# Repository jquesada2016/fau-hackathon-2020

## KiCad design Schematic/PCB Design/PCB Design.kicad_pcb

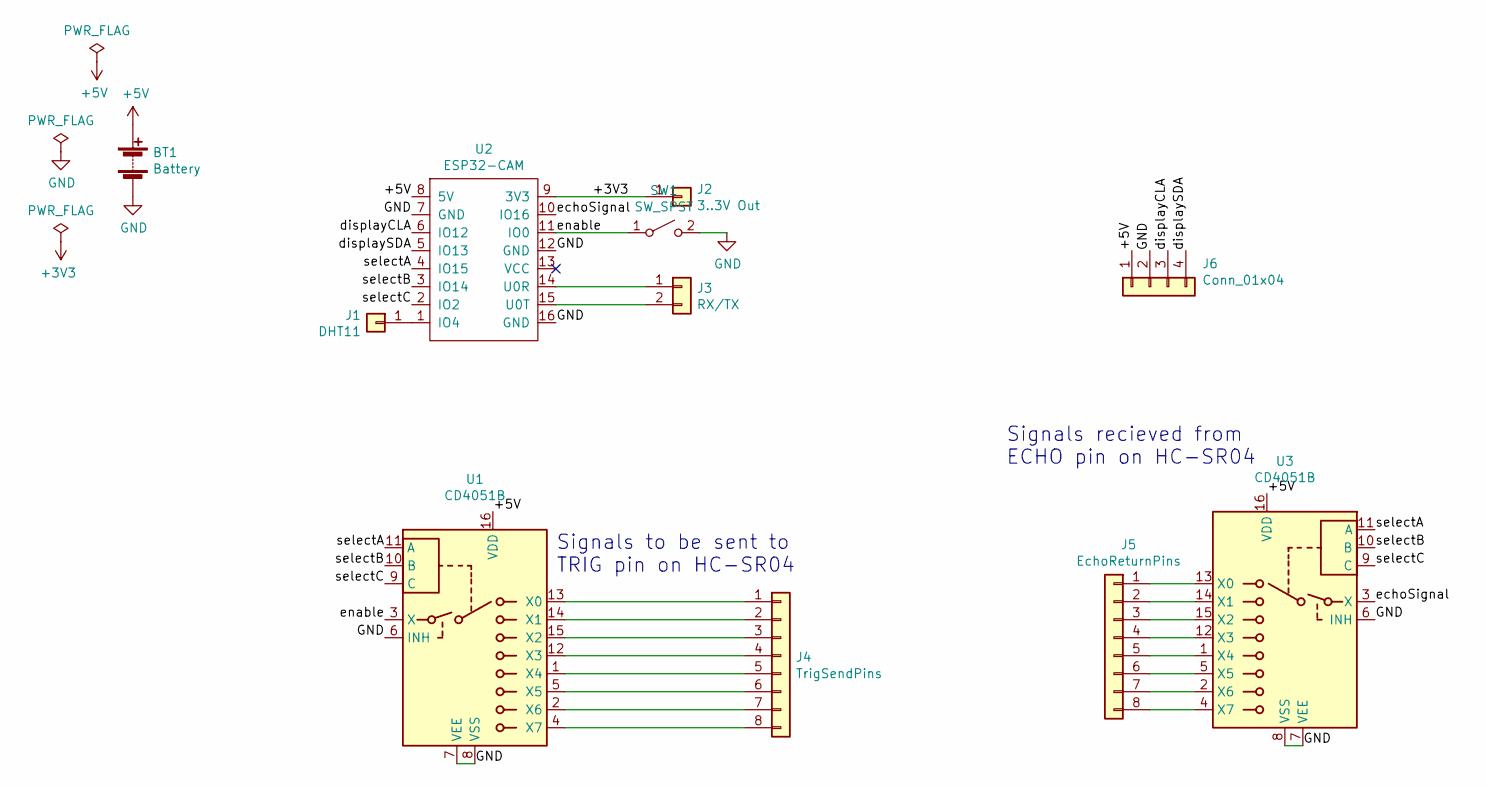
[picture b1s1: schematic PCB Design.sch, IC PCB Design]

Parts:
BT1: Battery; conn_01x02_battery
J1: DHT11; conn_01x01
J2: 3..3V Out; conn_01x01
J3: RX/TX; conn_01x02
J4: TrigSendPins; conn_01x08
J5: EchoReturnPins; conn_01x08
J6: Conn_01x04; conn_01x04
SW1: SW_SPST
U1, U3: CD4051B; DIP-16_W7.62mm
U2: ESP32-CAM; ESP32CAM

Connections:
+3V3: J2.1, U2.9 (3V3)
+5V: BT1.1 (+), J6.1, U1.16 (VDD), U2.8 (5V), U3.16 (VDD)
/displayCLA: J6.3, U2.6 (IO12)
/displaySDA: J6.4, U2.5 (IO13)
/echoSignal: U2.10 (IO16), U3.3 (X)
/enable: SW1.1 (A), U1.3 (X), U2.11 (IO0)
/selectA: U1.11 (A), U2.4 (IO15), U3.11 (A)
/selectB: U1.10 (B), U2.3 (IO14), U3.10 (B)
/selectC: U1.9 (C), U2.2 (IO2), U3.9 (C)
GND: BT1.2 (-), J6.2, SW1.2 (B), U1.6 (INH), U1.7 (VEE), U1.8 (VSS), U2.7 (GND), U2.12 (GND), U2.16 (GND), U3.6 (INH), U3.7 (VEE), U3.8 (VSS)
unnamed: J1.1, U2.1 (IO4)
unnamed: J3.1, U2.14 (U0R)
unnamed: J3.2, U2.15 (U0T)
unnamed: J4.1, U1.13 (X0)
unnamed: J4.2, U1.14 (X1)
unnamed: J4.3, U1.15 (X2)
unnamed: J4.4, U1.12 (X3)
unnamed: J4.5, U1.1 (X4)
unnamed: J4.6, U1.5 (X5)
unnamed: J4.7, U1.2 (X6)
unnamed: J4.8, U1.4 (X7)
unnamed: J5.1, U3.13 (X0)
unnamed: J5.2, U3.14 (X1)
unnamed: J5.3, U3.15 (X2)
unnamed: J5.4, U3.12 (X3)
unnamed: J5.5, U3.1 (X4)
unnamed: J5.6, U3.5 (X5)
unnamed: J5.7, U3.2 (X6)
unnamed: J5.8, U3.4 (X7)

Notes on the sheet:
Signals recieved from ECHO pin on HC-SR04
Signals to be sent to TRIG pin on HC-SR04

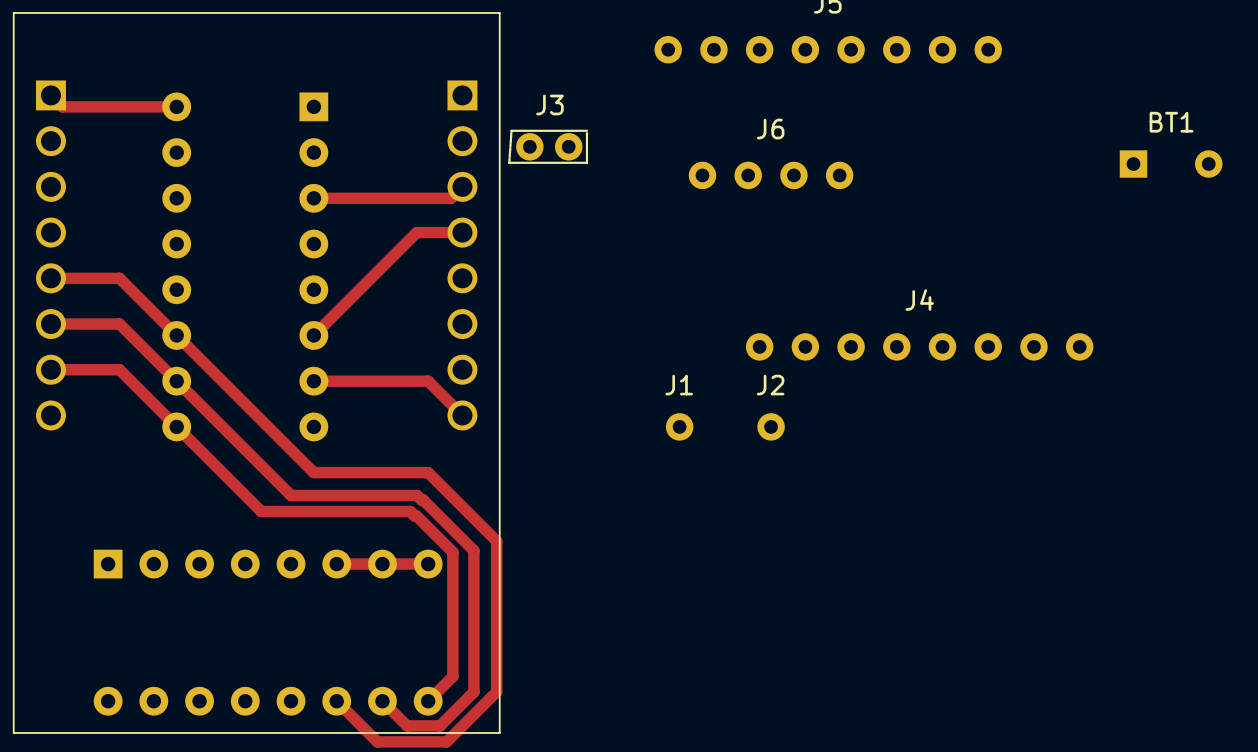
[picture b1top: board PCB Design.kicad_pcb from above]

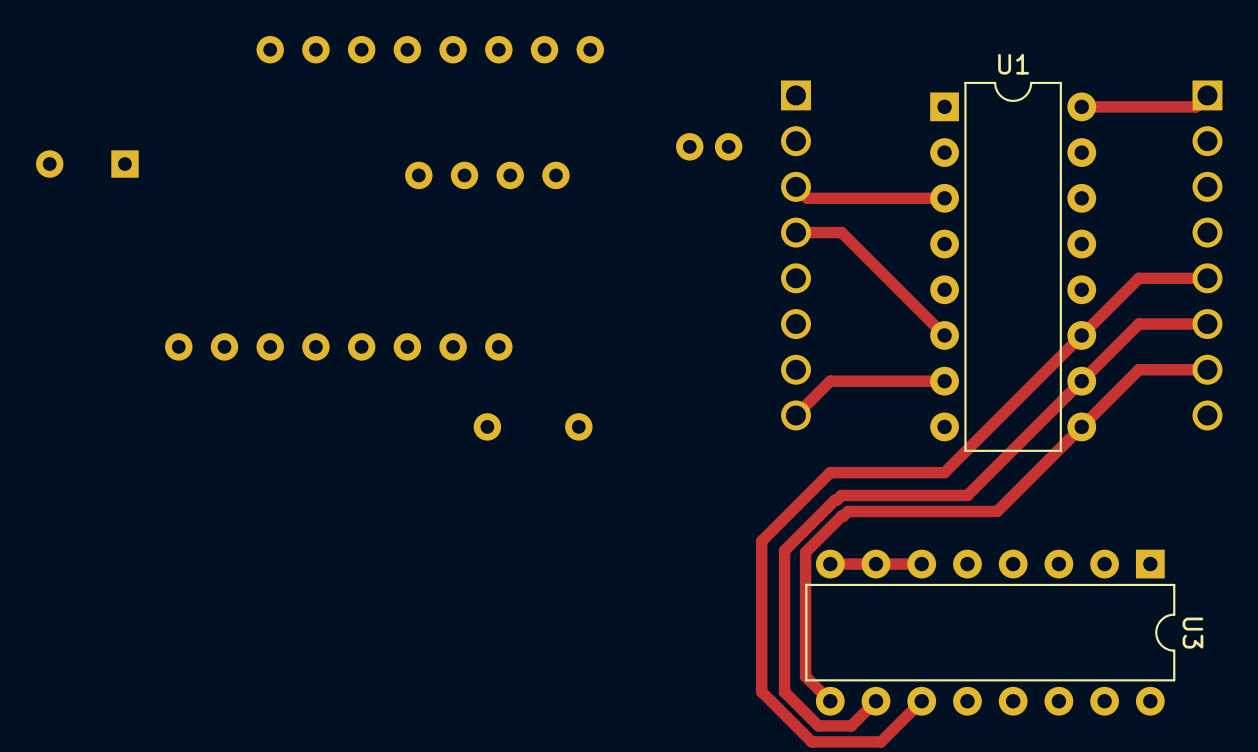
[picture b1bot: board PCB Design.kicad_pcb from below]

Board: 2 copper layers, 10 parts (2 on the bottom side), 29 nets.

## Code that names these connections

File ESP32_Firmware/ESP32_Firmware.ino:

#include "esp_camera.h"
#include <Wire.h>
#include <WiFi.h>
#include "SPIFFS.h"
#include "ESPAsyncWebServer.h"
#include "SSD1306.h"
#include <qrcode.h>

#define DHTTYPE DHT11


// Define pins
#define SELECTA0 15
#define SELECTA1 14
#define SELECTA2 2
#define ENABLE 4
#define ECHOSIGNAL 16
#define DISPLAYCLA 12
#define DISPLAYSDA 13
#define DHT11 0


// Function declerations
void select0();
void select1();
void select2();
void select3();
void select4();
void select5();
void select6();
void select7();

void findClosestObject(float values[]);
double getDistance(int sensorNumber);
void triggerSensor();
float getTemp();


SSD1306 display(0x3c, DISPLAYSDA, DISPLAYCLA);
QRcode qrcode(&display);
AsyncWebServer server(80);


const char* ssid = "Jose's Galaxy Note10+";
const char* password = "4077759622";


const char* file1 = "/index.html";
const char* file2 = "/app.js";
const char* file3 = "/styles.css";
const char* JAVASCRIPT = "text/javascript";
const char* CSS = "text/css";
const char* JSON = "text/json";


void setup() {
  Serial.begin(115200);
  Serial.setDebugOutput(true);
  Serial.println();

  // Pin mode setup
  pinMode(SELECTA0, OUTPUT);
  pinMode(SELECTA1, OUTPUT);
  pinMode(SELECTA2, OUTPUT);
  pinMode(DISPLAYSDA, OUTPUT);
  pinMode(DISPLAYCLA, OUTPUT);
  pinMode(ENABLE, OUTPUT);
  pinMode(ECHOSIGNAL, INPUT);
  pinMode(DHT11, INPUT);


  if (!SPIFFS.begin()) {
    Serial.println("it broke #SPIFFS");
  }
  WiFi.begin(ssid, password);

  while (WiFi.status() != WL_CONNECTED) {
    delay(500);
    Serial.print(".");
  }
  Serial.println("");
  Serial.println("WiFi connected");

  Serial.print("WiFi Ready! Use 'http://");
  Serial.print(WiFi.localIP());
  Serial.println("' to connect");

  // Create IP address link.
  const char* http = "http://";
  const String local_ip = WiFi.localIP().toString();
  const String address = http + local_ip;

  // Create web server routes
  server.on("/", HTTP_GET, [](AsyncWebServerRequest *request){
    Serial.println("Serving /");
    request->send(SPIFFS, "/index.html", "text/html");
  });
  server.on(file2, HTTP_GET, [](AsyncWebServerRequest *request) {
    Serial.println("Serving JS 1");
    request->send(SPIFFS, file2, JAVASCRIPT);
  });
  server.on(file3, HTTP_GET, [](AsyncWebServerRequest *request) {
    Serial.println("Serving JS 2");
    request->send(SPIFFS, file3, CSS);
  });
  server.on("/closestProximity", HTTP_GET, [](AsyncWebServerRequest *request) {
    Serial.println("Serving API call to /closestProximity");
    float values[2];
    findClosestObject(values);
    Serial.println("Finished findClossestObject()");

    String json = "{\"sensor\": " + String(values[0]) + ", \"distance\": " + String(values[1]) + "}";
    
    request->send(200, JSON, json);
  });
  
  
  server.begin();
  
  //display.init();
  //qrcode.init();

  // Display the address as a QR code.
  //qrcode.create(address);
}

void loop() {}


// Function definitions
void select0() {
  digitalWrite(SELECTA0, LOW);
  digitalWrite(SELECTA1, LOW);
  digitalWrite(SELECTA2, LOW);
}

void select1() {
  digitalWrite(SELECTA0, HIGH);
  digitalWrite(SELECTA1, LOW);
  digitalWrite(SELECTA2, LOW);
}

void select2() {
  digitalWrite(SELECTA0, LOW);
  digitalWrite(SELECTA1, HIGH);
  digitalWrite(SELECTA2, LOW);
}

void select3() {
  digitalWrite(SELECTA0, HIGH);
  digitalWrite(SELECTA1, HIGH);
  digitalWrite(SELECTA2, LOW);
}

void select4() {
  digitalWrite(SELECTA0, LOW);
  digitalWrite(SELECTA1, LOW);
  digitalWrite(SELECTA2, HIGH);
}

void select5() {
  digitalWrite(SELECTA0, HIGH);
  digitalWrite(SELECTA1, LOW);
  digitalWrite(SELECTA2, HIGH);
}

void select6() {
  digitalWrite(SELECTA0, LOW);
  digitalWrite(SELECTA1, HIGH);
  digitalWrite(SELECTA2, HIGH);
}

void select7() {
  digitalWrite(SELECTA0, HIGH);
  digitalWrite(SELECTA1, HIGH);
  digitalWrite(SELECTA2, HIGH);
}

void triggerSensor() {
  digitalWrite(ENABLE, LOW);
  delayMicroseconds(5);
  digitalWrite(ENABLE, HIGH);
  delayMicroseconds(10);
  digitalWrite(ENABLE, LOW);
}

float getTemp() {
  return 20 + 273.15;  
}

double getDistance(int sensorNumber) {
    switch (sensorNumber) {
      long duration;
      
      case 0:
        select0();
        triggerSensor();
        duration = pulseIn(ECHOSIGNAL, HIGH);
        return (duration/2.0) * (0.00002005 * sqrt(getTemp()));
      case 1:
        select1();
        triggerSensor();
        duration = pulseIn(ECHOSIGNAL, HIGH);
        return (duration/2.0) * (0.00002005 * sqrt(getTemp()));
      case 2:
        select2();
        triggerSensor();
        duration = pulseIn(ECHOSIGNAL, HIGH);
        return (duration/2.0) * (0.00002005 * sqrt(getTemp()));
      case 3:
        select3();
        triggerSensor();
        duration = pulseIn(ECHOSIGNAL, HIGH);
        return (duration/2.0) * (0.00002005 * sqrt(getTemp()));
      case 4:
        select4();
        triggerSensor();
        duration = pulseIn(ECHOSIGNAL, HIGH);
        return (duration/2.0) * (0.00002005 * sqrt(getTemp()));
      case 5:
        select5();
        triggerSensor();
        duration = pulseIn(ECHOSIGNAL, HIGH);
        return (duration/2.0) * (0.00002005 * sqrt(getTemp()));
      case 6:
        select6();
        triggerSensor();
        duration = pulseIn(ECHOSIGNAL, HIGH);
        return (duration/2.0) * (0.00002005 * sqrt(getTemp()));
      case 7:
        select7();
        triggerSensor();
        duration = pulseIn(ECHOSIGNAL, HIGH);
        return (duration/2.0) * (0.00002005 * sqrt(getTemp()));
      default:
        Serial.println("Error, you suck. The switch statement failed.");
        
    }
}

void findClosestObject(float values[]) {
  float distance = 9999999;
  for (int i = 0; i < 8; i++) {
    float current_distance = getDistance(i);
    if (current_distance < distance) {
      distance = current_distance;
      values[0] = i;
      values[1] = distance;
    }
  }
}

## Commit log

2020-02-10 set up git repo with initial implementation of QR Reader
2020-02-10 added redamentary QR scanning to ESP32
2020-02-13 created rough architectual schematic"
2020-02-14 added a 8 to 1 mux to select the sensor to listen to
2020-02-19 finished PCB
2020-02-28 Post Hackathon commit
2020-02-29 initiated rev 2A of the board design
2025-06-24 Bump pbkdf2 from 3.0.17 to 3.1.3 in /qrscanner
    ---
    updated-dependencies:
    - dependency-name: pbkdf2
    dependency-version: 3.1.3
    dependency-type: indirect
    ...
2025-07-17 Bump on-headers and compression in /qrscanner
    Bumps [on-headers](https://github.com/jshttp/on-headers) and [compression](https://github.com/expressjs/compression). These dependencies needed to be updated together.
    Updates `on-headers` from 1.0.2 to 1.1.0
    - [Release notes](https://github.com/jshttp/on-headers/releases)
    - [Changelog](https://github.com/jshttp/on-headers/blob/master/HISTORY.md)
    - [Commits](https://github.com/jshttp/on-headers/compare/v1.0.2...v1.1.0)
    Updates `compression` from 1.7.4 to 1.8.1
2025-08-21 Bump sha.js from 2.4.11 to 2.4.12 in /qrscanner
    Bumps [sha.js](https://github.com/crypto-browserify/sha.js) from 2.4.11 to 2.4.12.
    - [Changelog](https://github.com/browserify/sha.js/blob/master/CHANGELOG.md)
    - [Commits](https://github.com/crypto-browserify/sha.js/compare/v2.4.11...v2.4.12)
    ---
    updated-dependencies:
    - dependency-name: sha.js
2025-08-21 Bump cipher-base from 1.0.4 to 1.0.6 in /qrscanner
    Bumps [cipher-base](https://github.com/crypto-browserify/cipher-base) from 1.0.4 to 1.0.6.
    - [Changelog](https://github.com/browserify/cipher-base/blob/master/CHANGELOG.md)
    - [Commits](https://github.com/crypto-browserify/cipher-base/compare/v1.0.4...v1.0.6)
    ---
    updated-dependencies:
    - dependency-name: cipher-base
2025-09-10 Bump shell-quote and react-scripts in /qrscanner
    Bumps [shell-quote](https://github.com/ljharb/shell-quote) to 1.8.3 and updates ancestor dependency [react-scripts](https://github.com/facebook/create-react-app/tree/HEAD/packages/react-scripts). The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
    Updates `shell-quote` from 1.7.2 to 1.8.3
    - [Changelog](https://github.com/ljharb/shell-quote/blob/main/CHANGELOG.md)
    - [Commits](https://github.com/ljharb/shell-quote/compare/v1.7.2...v1.8.3)
    Updates `react-scripts` from 3.3.1 to 5.0.1
    - [Release notes](https://github.com/facebook/create-react-app/releases)
2025-11-18 Bump js-yaml from 3.13.1 to 3.14.2 in /qrscanner
    Bumps [js-yaml](https://github.com/nodeca/js-yaml) from 3.13.1 to 3.14.2.
    - [Changelog](https://github.com/nodeca/js-yaml/blob/master/CHANGELOG.md)
    - [Commits](https://github.com/nodeca/js-yaml/compare/3.13.1...3.14.2)
    ---
    updated-dependencies:
    - dependency-name: js-yaml
2025-11-27 Bump node-forge and react-scripts in /qrscanner
    Bumps [node-forge](https://github.com/digitalbazaar/forge) to 1.3.2 and updates ancestor dependency [react-scripts](https://github.com/facebook/create-react-app/tree/HEAD/packages/react-scripts). The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
    Updates `node-forge` from 0.9.0 to 1.3.2
    - [Changelog](https://github.com/digitalbazaar/forge/blob/main/CHANGELOG.md)
    - [Commits](https://github.com/digitalbazaar/forge/compare/0.9.0...v1.3.2)
    Updates `react-scripts` from 3.3.1 to 5.0.1
    - [Release notes](https://github.com/facebook/create-react-app/releases)
2025-12-31 Bump qs and react-scripts in /qrscanner
    Bumps [qs](https://github.com/ljharb/qs) to 6.14.1 and updates ancestor dependency [react-scripts](https://github.com/facebook/create-react-app/tree/HEAD/packages/react-scripts). These dependencies n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
    Updates `qs` from 6.7.0 to 6.14.1
    - [Changelog](https://github.com/ljharb/qs/blob/main/CHANGELOG.md)
    - [Commits](https://github.com/ljharb/qs/compare/v6.7.0...v6.14.1)
    Updates `react-scripts` from 3.3.1 to 5.0.1
    - [Release notes](https://github.com/facebook/create-react-app/releases)
2026-01-17 Bump tar and fsevents in /qrscanner
    Removes [tar](https://github.com/isaacs/node-tar). It's no longer used after updating ancestor dependency [fsevents](https://github.com/fsevents/fsevents). These dependencies need to be updated toget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
    Removes `tar`
    Updates `fsevents` from 1.2.11 to 1.2.13
    - [Release notes](https://github.com/fsevents/fsevents/releases)
    - [Commits](https://github.com/fsevents/fsevents/compare/v1.2.11...v1.2.13)
    ---
2026-01-24 Bump lodash from 4.17.15 to 4.17.23 in /qrscanner
    Bumps [lodash](https://github.com/lodash/lodash) from 4.17.15 to 4.17.23.
    - [Release notes](https://github.com/lodash/lodash/releases)
    - [Commits](https://github.com/lodash/lodash/compare/4.17.15...4.17.23)
    ---
    updated-dependencies:
    - dependency-name: lodash
2026-02-04 Bump url-parse from 1.4.7 to 1.5.10 in /qrscanner
    Bumps [url-parse](https://github.com/unshiftio/url-parse) from 1.4.7 to 1.5.10.
    - [Commits](https://github.com/unshiftio/url-parse/compare/1.4.7...1.5.10)
    ---
    updated-dependencies:
    - dependency-name: url-parse
    dependency-version: 1.5.10
2026-02-05 Bump semver and react-scripts in /qrscanner
    Bumps [semver](https://github.com/npm/node-semver) to 7.7.3 and updates ancestor dependency [react-scripts](https://github.com/facebook/create-react-app/tree/HEAD/packages/react-scripts). These depen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
    Updates `semver` from 5.7.1 to 7.7.3
    - [Release notes](https://github.com/npm/node-semver/releases)
    - [Changelog](https://github.com/npm/node-semver/blob/main/CHANGELOG.md)
    - [Commits](https://github.com/npm/node-semver/compare/v5.7.1...v7.7.3)
    Updates `react-scripts` from 3.3.1 to 5.0.1
2026-02-13 Bump qs and react-scripts in /qrscanner
    Bumps [qs](https://github.com/ljharb/qs) to 6.14.2 and updates ancestor dependency [react-scripts](https://github.com/facebook/create-react-app/tree/HEAD/packages/react-scripts). These dependencies n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
    Updates `qs` from 6.7.0 to 6.14.2
    - [Changelog](https://github.com/ljharb/qs/blob/main/CHANGELOG.md)
    - [Commits](https://github.com/ljharb/qs/compare/v6.7.0...v6.14.2)
    Updates `react-scripts` from 3.3.1 to 5.0.1
    - [Release notes](https://github.com/facebook/create-react-app/releases)
